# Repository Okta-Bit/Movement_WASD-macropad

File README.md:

# Movement_WASD-macropad
# move_second2

This design was inspired of the Stardance Hackpad example and i used hexagon design.

This Keypad was design to be used to move a character and can alsom be used to play low game in the firmware like tetris, snake, or POP CAT? 

Schematics

Project Board
This is  my first time using Kicad, thats why i'm bit lazzy at this stage.

* Keyboard Maintainer: [Okta](https://github.com/Okta-Bit)
* Hardware Supported: PCB, er-oled 0.91-1w-i2c, Rotary Encoder, SEED XIAO RP2040, switch push button, SK6812 MINI-E LEDs.
* Hardware Availability: 
(Region = Indonesia)
er-oled 0.91-1w-i2c = https://shopee.co.id/product/26567324/3220617409 (2.33 euro/pcs)
Rotary Encoder = https://shopee.co.id/product/5062292/27924224647 (0.44 euro/pcs)
SEED XIAO RP2040 = https://shopee.co.id/product/27499686/14661809771 (6.59 euro/pcs)
SK6812 MINI-E LEDs = https://shopee.co.id/product/199826381/27626598164 (0.09 euro/pcs) x 3 = 0.36 euro
push button keyboard = https://shopee.co.id/product/31228096/16586392506 (0.08 euro/pcs) x 4 = 0.32 euro
Material price total = 10.04 euro = Rp 206.000

Example of this keyboard:

This macropad works for inputing W, A, S, and D word only and suitable for gaming activities and also it can increase and decrease volume using rotary encoder. This project was design to complete Stardance mission and increase knowledge about keyboard.

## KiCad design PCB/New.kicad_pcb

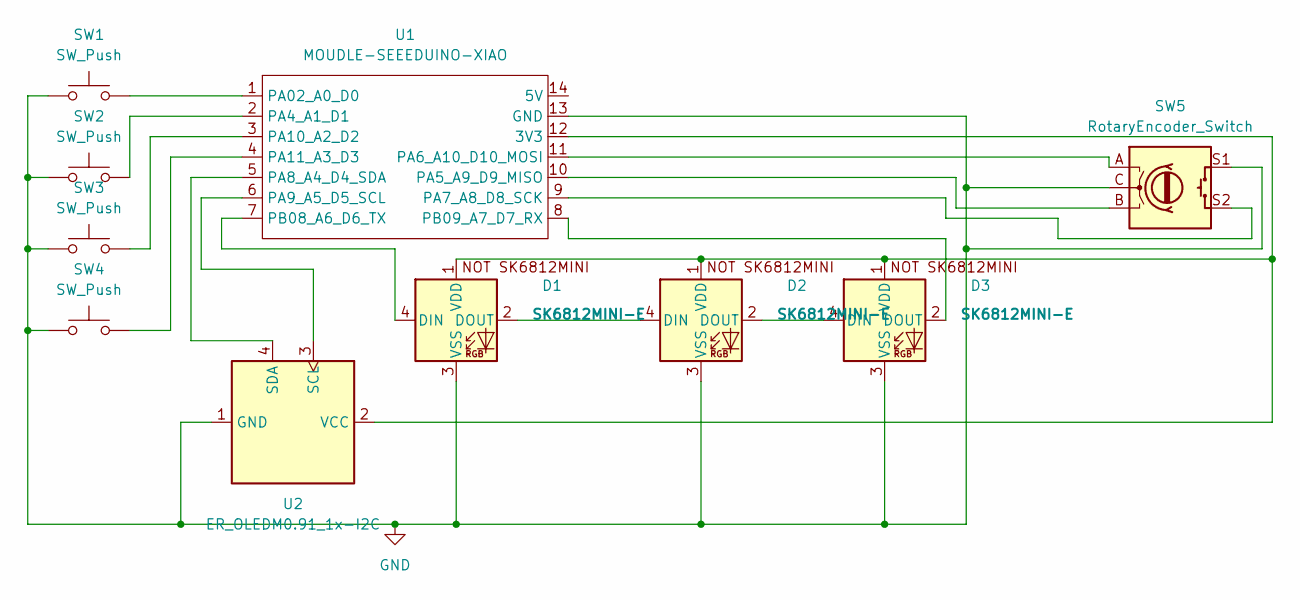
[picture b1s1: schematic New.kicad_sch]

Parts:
D1, D2, D3: SK6812MINI-E; SK6812MINI-E_fixed
SW1, SW2, SW3, SW4: SW_Push; SW_Cherry_MX_1.00u_PCB
SW5: RotaryEncoder_Switch; RotaryEncoder_Alps_EC11E-Switch_Vertical_H20mm
U1: MOUDLE-SEEEDUINO-XIAO; XIAO-Generic-Hybrid-14P-2.54-21X17.8MM
U2: ER_OLEDM0.91_1x-I2C

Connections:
GND: D1.3 (VSS), D2.3 (VSS), D3.3 (VSS), SW1.1, SW2.1, SW3.1, SW4.1, SW5.C, SW5.S1, U1.13 (GND), U2.1 (GND)
unnamed: D1.4 (DIN), U1.7 (PB08_A6_D6_TX)
unnamed: D1.2 (DOUT), D2.4 (DIN)
unnamed: D1.1 (VDD), D2.1 (VDD), D3.1 (VDD), U1.12 (3V3), U2.2 (VCC)
unnamed: D2.2 (DOUT), D3.4 (DIN)
unnamed: D3.2 (DOUT), U1.8 (PB09_A7_D7_RX)
unnamed: SW1.2, U1.1 (PA02_A0_D0)
unnamed: SW2.2, U1.2 (PA4_A1_D1)
unnamed: SW5.B, U1.10 (PA5_A9_D9_MISO)
unnamed: SW5.A, U1.11 (PA6_A10_D10_MOSI)
unnamed: SW5.S2, U1.9 (PA7_A8_D8_SCK)
unnamed: U1.5 (PA8_A4_D4_SDA), U2.4 (SDA)
unnamed: U1.6 (PA9_A5_D5_SCL), U2.3 (SCL)
unnamed: SW3.2, U1.3 (PA10_A2_D2)
unnamed: SW4.2, U1.4 (PA11_A3_D3)

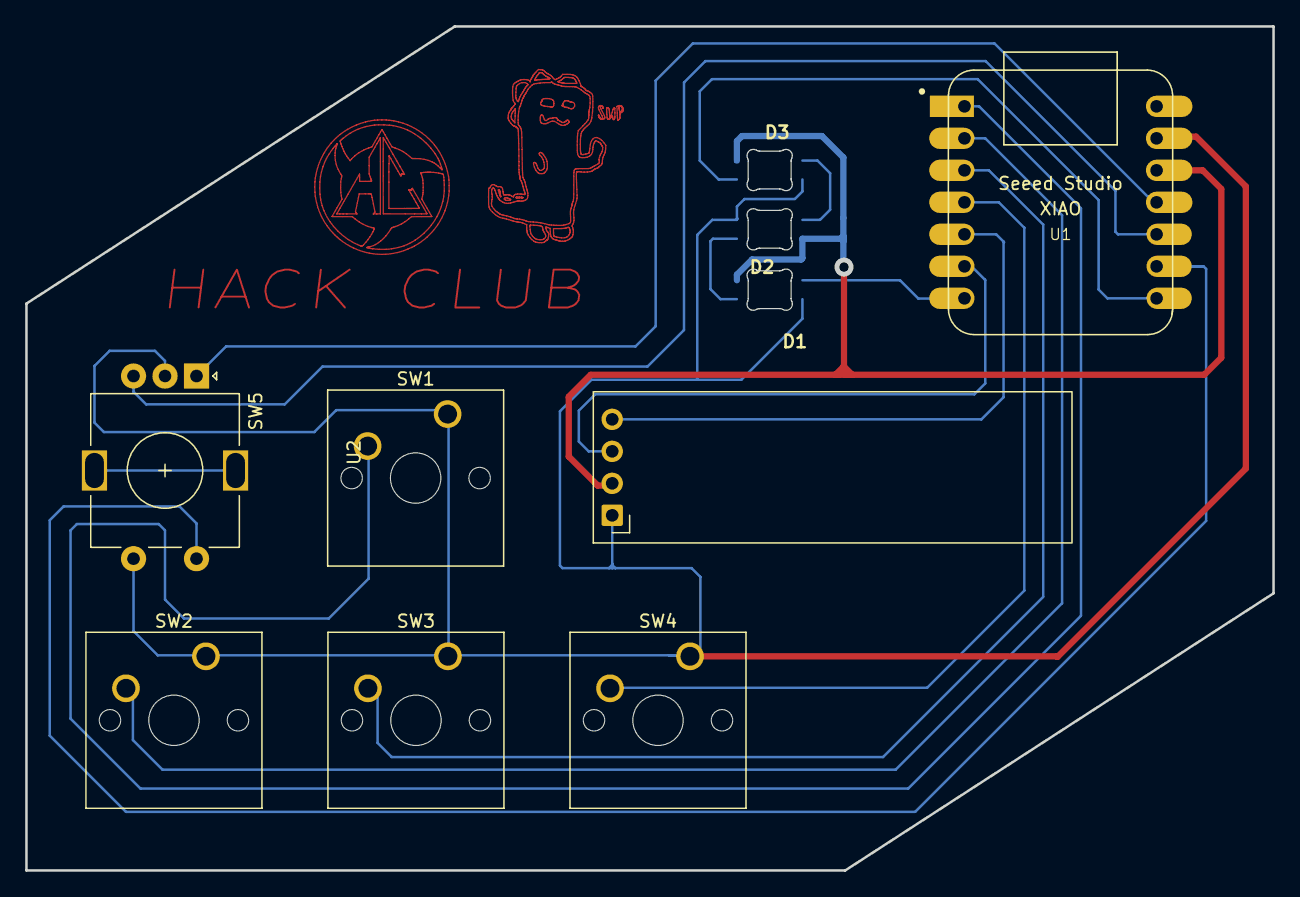
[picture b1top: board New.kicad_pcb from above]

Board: 2 copper layers, 99.0 x 67.0 mm, 10 parts (0 on the bottom side), 15 nets.
